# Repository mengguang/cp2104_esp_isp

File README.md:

# cp2104_esp_isp
programming esp8266 or esp32 using cp2104 usb to uart converter.

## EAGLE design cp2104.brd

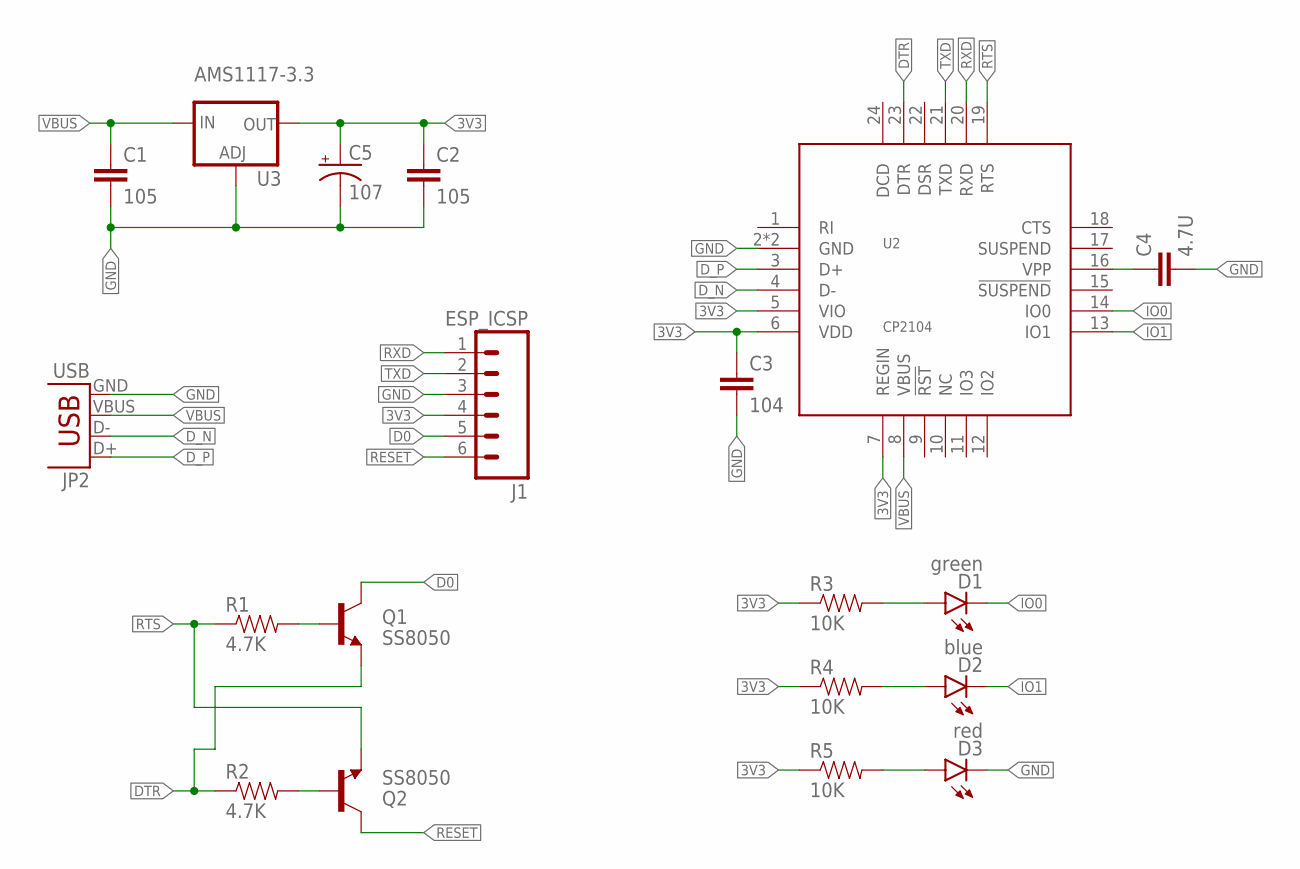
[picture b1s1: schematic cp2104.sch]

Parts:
C1, C2: 105; 0603-CAP
C3: 104; 0603-CAP
C4: 4.7U; 0603-CAP
C5: 107; EIA3528
D1: green; LED-0603-SEEED
D2: blue; LED-0603-SEEED
D3: red; LED-0603-SEEED
J1: ESP_ICSP; 1X06_NO_SILK
JP2: USB; MICROUSB-U-F-M5DD-Y-1
Q1, Q2: SS8050; SOT23-3-JLC
R1, R2: 4.7K; 0603-RES
R3, R4, R5: 10K; 0603-RES
U2: CP2104; QFN24
U3: AMS1117-3.3; SOT223

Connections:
3V3: C2.1, C3.1, C5.A (+), J1.4, R3.1, R4.1, R5.1, U2.5 (VIO), U2.6 (VDD), U2.7 (REGIN), U3.2 (OUT), U3.4 (OUT)
D0: J1.5, Q1.3 (C)
DTR: Q1.2 (E), R2.1, U2.23 (DTR)
D_N: JP2.D-, U2.4 (D-)
D_P: JP2.D+, U2.3 (D+)
GND: C1.2, C2.2, C3.2, C4.2, C5.C (-), D3.- (C), J1.3, JP2.GND, U2.2 (GND), U2.25 (GND), U3.1 (ADJ)
IO0: D1.- (C), U2.14 (IO0)
IO1: D2.- (C), U2.13 (IO1)
unnamed: C4.1, U2.16 (VPP)
unnamed: D3.+ (A), R5.2
unnamed: D1.+ (A), R3.2
unnamed: D2.+ (A), R4.2
unnamed: Q1.1 (B), R1.2
unnamed: Q2.1 (B), R2.2
RESET: J1.6, Q2.3 (C)
RTS: Q2.2 (E), R1.1, U2.19 (RTS)
RXD: J1.1, U2.20 (RXD)
TXD: J1.2, U2.21 (TXD)
VBUS: C1.1, JP2.VBUS, U2.8 (VBUS), U3.3 (IN)

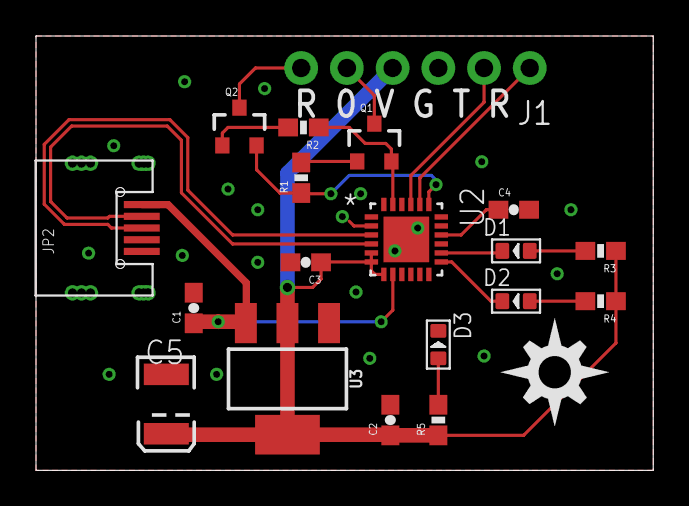
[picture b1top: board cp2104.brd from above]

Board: 2 copper layers, 34.3 x 24.1 mm, 20 parts (0 on the bottom side), 19 nets.

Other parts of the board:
U$1: DIYNOVA_LOGO

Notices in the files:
parts and their libraries:
SparkFun-Connectors: Licensing: Creative Commons ShareAlike 4.0 International - https://creativecommons.org/licenses/by-sa/4.0
